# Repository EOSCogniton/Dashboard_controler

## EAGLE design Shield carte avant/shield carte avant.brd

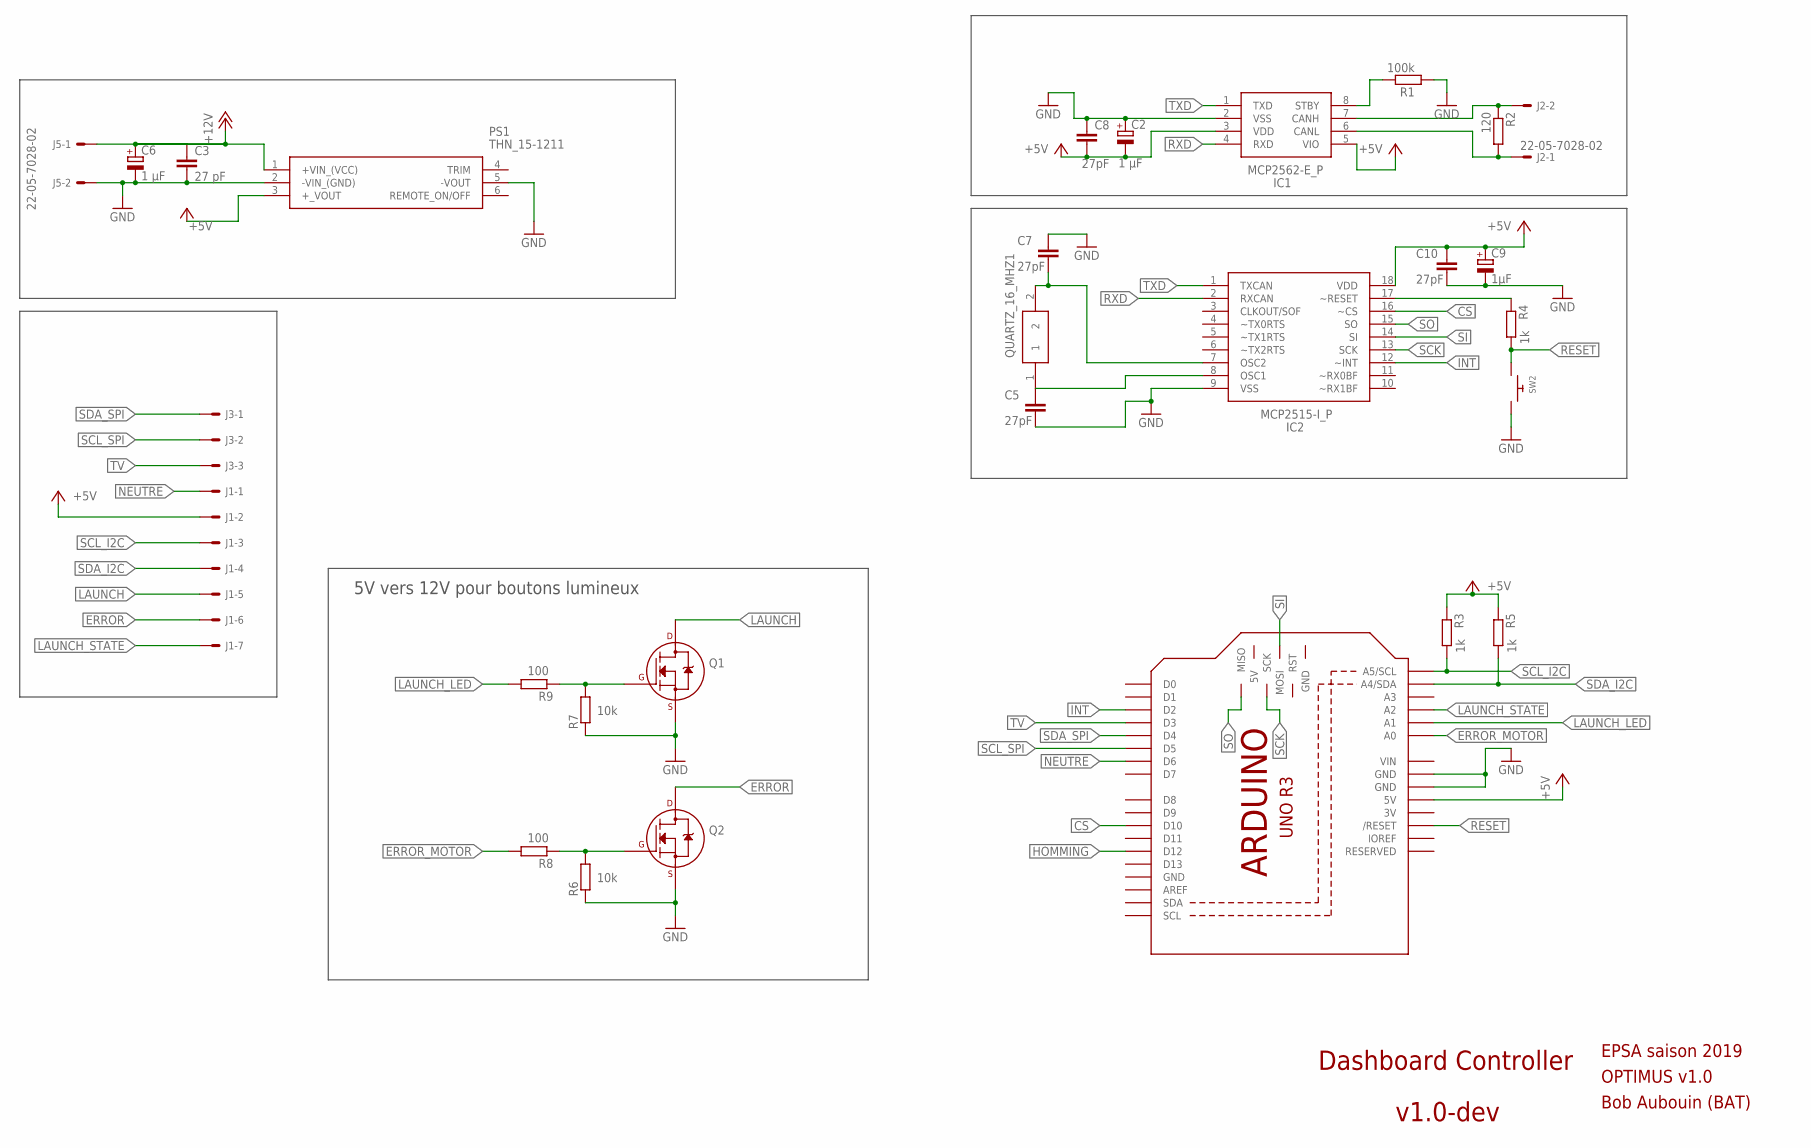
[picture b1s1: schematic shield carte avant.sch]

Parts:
C2, C6: 1 µF; B45181A
C3: 27 pF; C025-024X044
C5, C7, C8, C10: 27pF; C025-030X050
C9: 1µF; B45181A
IC1: MCP2562-E_P; DIP781W56P254L950H533Q8N
IC2: MCP2515-I_P; DIP254P762X432-18
J1: 22-05-7078-07; 7395-07
J2, J5: 22-05-7028-02; 7395-02
J3: 22-05-7038-03; 7395-03
M1: ARDUINO_R3_ICSP; ARDUINOR3_ICSP
PS1: THN_15-1211; THN-15-SERIES
Q1, Q2: 2N7000_TO92; TO-92
QUARTZ_16_MHZ1: FOXSLF_160-20; HC49SLF_1
R1: 100k; 0204/7
R2: 120; 0204/7
R3, R4, R5: 1k; 0204/7
R6, R7: 10k; 0204/7
R8, R9: 100; 0204/7
SW2: SWITCH_PUSHBUTTONEVQ-PE; TACT_PANA-EVQ

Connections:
3V: M1.3V
+5V: C2.-, C8.2, C9.+, C10.1, IC1.3 (VDD), IC2.18 (VDD), J1.2, M1.5V, PS1.3 (+_VOUT), R3.1, R5.1
+12V: C3.1, C6.+, J5.1, PS1.1 (+VIN_(VCC))
CS: IC2.16 (~CS), M1.D10
ERROR: J1.6, Q2.3 (D)
ERROR_MOTOR: M1.A0, R8.2
GND: C2.+, C3.2, C5.2, C6.-, C7.1, C8.1, C9.-, C10.2, IC1.2 (VSS), IC2.9 (VSS), J5.2, M1.GND, M1.GND@1 (GND), M1.GND@3 (GND), PS1.2 (-VIN_(GND)), PS1.5 (-VOUT), Q1.1 (S), Q2.1 (S), R1.1, R6.1, R7.1, SW2.P$2
HOMMING: M1.D12
INT: IC2.12 (~INT), M1.D2
LAUNCH: J1.5, Q1.3 (D)
LAUNCH_LED: M1.A1, R9.2
LAUNCH_STATE: J1.7, M1.A2
unnamed: IC1.8 (STBY), R1.2
unnamed: C5.1, IC2.8 (OSC1), QUARTZ_16_MHZ1.1
unnamed: IC1.7 (CANH), J2.2, R2.1
unnamed: C7.2, IC2.7 (OSC2), QUARTZ_16_MHZ1.2
unnamed: IC1.6 (CANL), J2.1, R2.2
unnamed: IC2.17 (~RESET), R4.1
unnamed: Q2.2 (G), R6.2, R8.1
unnamed: Q1.2 (G), R7.2, R9.1
NEUTRE: J1.1, M1.D6
RESET: M1.RESET (/RESET), R4.2, SW2.P$1
RXD: IC1.4 (RXD), IC2.2 (RXCAN)
SCK: IC2.13 (SCK), M1.SCK
SCL_I2C: J1.3, M1.A5 (A5/SCL), R3.2
SCL_SPI: J3.2, M1.D5
SDA_I2C: J1.4, M1.A4 (A4/SDA), R5.2
SDA_SPI: J3.1, M1.D4
SI: IC2.14 (SI), M1.MOSI
SO: IC2.15 (SO), M1.MISO
TV: J3.3, M1.D3
TXD: IC1.1 (TXD), IC2.1 (TXCAN)
VIN: M1.VIN

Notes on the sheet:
Dashboard Controller
v1.0-dev
EPSA saison 2019
OPTIMUS v1.0
Bob Aubouin (BAT)
5V vers 12V pour boutons lumineux

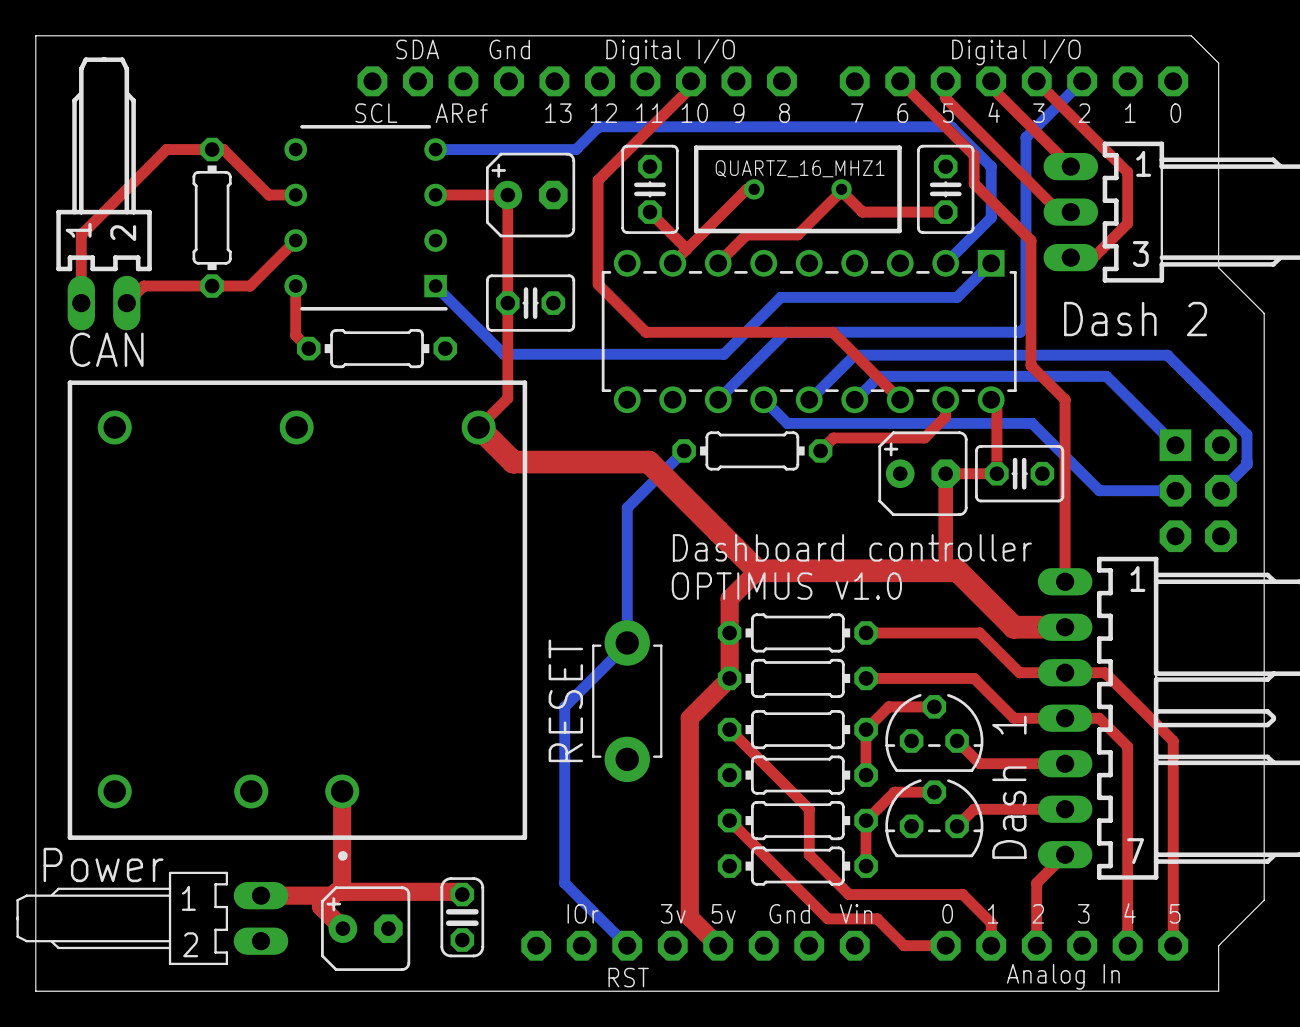
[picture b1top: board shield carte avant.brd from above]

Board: 2 copper layers, 68.6 x 53.3 mm, 29 parts (0 on the bottom side), 30 nets.

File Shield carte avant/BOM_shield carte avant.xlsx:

Qty | Value | Device | Description | Dispo au garage ? | Référence RS |  |  |  |  | oui
2 |  | 2N7000_TO92 | 2N7000, 2N7002, NDS7002A | oui | 671-4733 |  |  |  |  | non
1 |  | SWITCH_PUSHBUTTONEVQ-PE | Buttons | non | 734-6823 |  |  |  |  | Je sais pas
3 | 1 µF | CPOL-EUB45181A | POLARIZED CAPACITOR, European symbol | oui
2 | 100 | R-EU_0204/7 | RESISTOR, European symbol | oui
1 | 100k | R-EU_0204/7 | RESISTOR, European symbol | oui
2 | 10k | R-EU_0204/7 | RESISTOR, European symbol | oui
1 | 120 | R-EU_0204/7 | RESISTOR, European symbol | oui
3 | 1k | R-EU_0204/7 | RESISTOR, European symbol | oui
2 | 22-05-7028-02 | 22-05-7028-02 | CONNECTOR | Je sais pas | 173-2916
1 | 22-05-7038-03 | 22-05-7038-03 | CONNECTOR | Je sais pas | 173-2922
1 | 22-05-7078-07 | 22-05-7078-07 | CONNECTOR | Je sais pas | 173-2972
3 | 27pF | C-EU025-030X050 | CAPACITOR, European symbol | oui
2 | 680 pF | C-EU025-024X044 | CAPACITOR, European symbol | Je sais pas
1 | ARDUINO_R3_ICSP | ARDUINO_R3_ICSP | Arduino Uno | non | 769-7409
1 | FOXSLF_160-20 | FOXSLF_160-20 | Crystal 16.000MHz | non | 547-6294
1 | MCP2515-I_P | MCP2515-I_P | Stand-Alone CAN Controller | non | 628-3532
1 | MCP2562-E_P | MCP2562-E_P | CAN Transceiver | non | 799-0225 |  |  | 2N700
1 | THN_15-1211 | THN_15-1211 | TRACOPOWER Isolated DC-DC Converter | non | 438-272

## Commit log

2018-12-04 travail dèjà fait
2018-12-13 Déplacement de composant pour faire de la place pour les relais
2018-12-17 Ajout de la documentation du shield CANdiy
2018-12-17 Ajout des librairie mcp2515 et 2562 traversant
2018-12-17 Alimentation de l'arduino par le 5V, passage des ic CAN en traversant et correction du schéma CAN
2018-12-17 Ajout des résistance de tirage de l'I2C
2018-12-17 Ajout des nouveaux vias
2018-12-18 Début ajout relais pour les boutons lumineux
2019-01-03 Ajout des MOSFET pour gérer l'affichage des boutons
2019-01-05 Fin du routage et vérification sérigraphie
2019-01-13 Ajout du readme
2019-01-13 Sérigraphie
2019-01-13 Ajout BOM
2019-01-17 ajout du gitignore
2019-01-17 Revue PJR
2019-01-17 maj numéro de version pour release
2019-01-20 Supression de librairie inutile
2019-01-20 Légères modifs avant envoie en prod
2019-01-20 Ajout des fichiers gerbers
